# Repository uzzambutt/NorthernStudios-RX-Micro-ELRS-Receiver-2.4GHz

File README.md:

<p align="center">

</p>

<h1 align="center">Nano 2.4 GHz ExpressLRS Diversity PA/LNA Receiver</h1>

<p align="center">
  <strong>An ultra-compact (18×24 mm), open-hardware 2.4 GHz ExpressLRS receiver featuring true antenna diversity, a high-power FEM (+20 dBm telemetry), integrated Wi-Fi ceramic antenna, and paneled breakaway rails for low-cost JLCPCB PCBA.</strong>
</p>

<p align="center">
  <a href="#key-specifications--features">Key Specs</a> •
  <a href="#hero-visuals--3d-views">Visuals</a> •
  <a href="#schematic--system-architecture">Architecture</a> •
  <a href="#hardware-configuration--pinout">Pinout</a> •
  <a href="#pcb-fabrication--stackup-requirements">PCB Stackup</a> •
  <a href="#flashing--firmware-setup">Firmware Setup</a> •
  <a href="#bill-of-materials-bom--sourcing">BOM</a> •
  <a href="#license--regulatory-compliance">License</a>
</p>

---

## 1. Hero Visuals & 3D Views

<p align="center">
  
  <br>
  <em>Figure 1: Production 3D Top Render of the Nano 2.4 GHz ExpressLRS Diversity PA/LNA Receiver</em>
</p>

<details open>
<summary><b>🔍 Detailed 3D Perspective Comparison (Front & Back Views)</b></summary>
<br>

| Front Perspective (Core Silicon & RF Frontend) | Back Perspective (Passives, Testpads & Ground Plane) |
| :---: | :---: |
|  |  |
| **Top Side (L1):** ESP32-C3FH4, Semtech SX1280 Transceiver, Skyworks SE2431L PA/LNA FEM, 2450FM07D0034 Bandpass Filter, dual U.FL IPEX jacks, Johanson 2450AT ceramic chip antenna, status LED, crystals, and JST-GH connector. | **Bottom Side (L4):** Solid thermal relief stitching vias, dedicated USB test pads (USBD+/USBD-), BOOT strapping testpad, and low-impedance RF ground shield flood. |

</details>

---

## 2. Key Specifications & Features

The **NorthernStudios Nano 2.4 GHz ExpressLRS Diversity Receiver** is engineered for long-range, high-reliability UAV control links, telemetry backhaul, and high-interference drone racing / freestyle environments. Combining high-efficiency RISC-V computing with Semtech's SX1280 transceiver and Skyworks' SE2431L front-end module, it provides industrial-grade packet reception sensitivity, +20 dBm (100 mW) telemetry uplink, and seamless over-the-air firmware management.

### Executive Specification Matrix

| Category | Specification | Technical Implementation / Notes |
| :--- | :--- | :--- |
| **Microcontroller (MCU)** | **ESP32-C3FH4** | 32-bit RISC-V single-core @ 160 MHz, 400 KB SRAM, 4 MB embedded SiP SPI flash |
| **RF Transceiver** | **Semtech SX1280IMLTRT** | 2.4 GHz LoRa, FLRC, and high-speed FSK modulation engine (-132 dBm sensitivity) |
| **Front-End Module (FEM)** | **Skyworks SE2431L** | Fully integrated RF front-end: +22 dB PA, +12.5 dB LNA (2.0 dB NF), SP3T RF switch |
| **Telemetry Uplink Power** | **Up to 100 mW (+20 dBm)** | Dynamic/fixed telemetry power configurable via ExpressLRS WebUI and Lua scripts |
| **Primary Antenna Link** | **Dual U.FL / IPEX1 (ANT1 / ANT2)** | True spatial and polarization diversity switched dynamically per-packet |
| **Configuration Link** | **Johanson 2450AT18A100** | Dedicated onboard 2.45 GHz ceramic chip antenna for ESP32 Wi-Fi AP & WebUI |
| **RF Filtering** | **Johanson 2450FM07D0034** | Matched high-rejection 2.4 GHz ceramic bandpass filter / balun |
| **Active PCB Dimensions** | **16.0 × 22.0 mm** | Ultra-lightweight form factor suitable for sub-250g micros and long-range wings |
| **Board Interface Pads** | **2.54 mm Castellated Edges** | 4-pin direct solder pads (`5V`, `GND`, `TX`, `RX`) + sub-miniature test points |
| **Quick-Disconnect Plug** | **JST-GH 4-Pin Horizontal** | Standard 1.25 mm pitch connector for direct drone flight controller wire harness |
| **Panelized Manufacturing** | **70.0 × 70.0 mm Breakaway** | 0.6 mm perforated mouse-bite tabs, optical fiducials, and 3.2 mm tooling holes |
| **Power Input Range** | **4.5 V – 5.5 V DC** | Onboard high-efficiency, low-noise TSOT-23-5 LDO producing clean 3.3 V @ 500 mA |
| **Firmware Ecosystem** | **ExpressLRS v3.x / v4.x** | Custom unified target definition via runtime `hardware.json` or config profiles |

---

## 3. Schematic & Architecture

### System Schematic
The schematic is captured in KiCad 8/9 with complete hierarchical decoupling, controlled RF coplanar waveguides, and low-noise power distribution.

<p align="center">
  
  <br>
  <em>Figure 2: Complete Electrical Schematic — ESP32-C3FH4 Core, SX1280 2.4 GHz Transceiver, SE2431L Front-End Module, and Johanson RF Network</em>
</p>

### Architecture & Signal Flow

The receiver features two independent 2.4 GHz RF paths:
1. **LoRa / FLRC Flight Control Path:** Routes bidirectional RF signals between dual external U.FL dipole/immortal-T antennas, through the SE2431L SP3T switch, through the internal PA/LNA, through the matched 2450FM07D0034 bandpass filter, and into the Semtech SX1280 transceiver.
2. **Wi-Fi WebUI Configuration Path:** Connects the ESP32-C3's internal Wi-Fi/Bluetooth RF transceiver (`LNA_IN`) directly to an onboard Johanson 2450AT ceramic chip antenna through a precision 50Ω Grounded Coplanar Waveguide (GCPW), isolating telemetry link tuning from configuration management.

```mermaid
flowchart LR
    subgraph Antennas ["Antenna System"]
        A1["U.FL Antenna 1 (ANT1)"]
        A2["U.FL Antenna 2 (ANT2)"]
        AC["Johanson 2450AT Chip Antenna"]
    end

    subgraph FrontEnd ["RF Front-End (FEM)"]
        SW{"SE2431L SP3T Switch"}
        PA["Power Amp (+22 dB)"]
        LNA["Low Noise Amp (+12.5 dB)"]
    end

    subgraph Filtering ["RF Conditioning"]
        BPF["Johanson 2450FM07D0034 Filter"]
    end

    subgraph Silicon ["Core Transceiver & Processing"]
        SX["Semtech SX1280 Transceiver"]
        ESP["Espressif ESP32-C3FH4 (RISC-V)"]
    end

    subgraph Host ["Flight Controller Interface"]
        FC["Flight Controller (CRSF UART)"]
    end

    A1 <-->|"50Ω GCPW"| SW
    A2 <-->|"50Ω GCPW"| SW
    SW <-->|"TX Mode"| PA
    SW <-->|"RX Mode"| LNA
    PA <--> BPF
    LNA <--> BPF
    BPF <-->|"Balanced RF"| SX
    SX <-->|"High-Speed SPI + IRQ"| ESP
    AC <-->|"50Ω GCPW (Wi-Fi 802.11b/g/n)"| ESP
    ESP <-->|"CRSF Protocol (420k / 921k Baud)"| FC
```

#### ASCII Architecture Reference
```text
+---------------------------------------------------------------------------------------+
|                                    ANTENNA SYSTEM                                     |
|    [U.FL Port 1]                     [U.FL Port 2]            [Johanson 2450AT Chip]  |
|          |                                 |                             |            |
|          +----------------+----------------+                             |            |
|                           | (50Ω GCPW)                                   | (50Ω GCPW) |
|                           v                                              |            |
|       +---------------------------------------+                          |            |
|       |         Skyworks SE2431L FEM          |                          |            |
|       |  [ANT Switch] <-> [PA / +22dB]        |                          |            |
|       |               <-> [LNA / +12.5dB]     |                          |            |
|       +-------------------+-------------------+                          |            |
|                           ^                                              |            |
|                           | (Tx / Rx Enable & Ant Sel)                   |            |
|                           v                                              |            |
|       +---------------------------------------+                          |            |
|       |     Johanson 2450FM07D0034 Filter     |                          |            |
|       +-------------------+-------------------+                          |            |
|                           | (Matched Differential)                       |            |
|                           v                                              |            |
|       +---------------------------------------+                          |            |
|       |       Semtech SX1280 Transceiver      |                          |            |
|       |        2.4 GHz LoRa / FLRC / FSK      |                          |            |
|       +-------------------+-------------------+                          |            |
|                           |                                              |            |
|                           | SPI Bus (MOSI, MISO, SCK, NSS, BUSY, DIO1)   |            |
|                           v                                              v            |
|       +-----------------------------------------------------------------------+       |
|       |                     Espressif ESP32-C3FH4 Core                        |       |
|       |          32-bit RISC-V @ 160 MHz | 4MB Flash | 2.4 GHz Wi-Fi          |       |
|       +-----------------------------------+-----------------------------------+       |
|                                           |                                           |
|                           CRSF Telemetry  |  CRSF Serial RX                           |
|                           (GPIO20 - TX)   |  (GPIO21 - RX)                            |
|                                           v                                           |
|                         [Flight Controller UART Pad / JST-GH]                         |
+---------------------------------------------------------------------------------------+
```

---

## 4. Hardware Configuration & Pinout

The pin assignment is optimized for optimal trace routing on 4-layer PCBs, preserving signal integrity along high-speed SPI lines while isolating sensitive radio triggers from high-frequency clock harmonics.

### ExpressLRS Hardware Pin Mapping

| ESP32-C3 GPIO | Function / Net | ExpressLRS Definition | Description | Electrical Notes |
| :--- | :--- | :--- | :--- | :--- |
| **GPIO02** | `SX_RST` | `radio_rst` | SX1280 Hardware Reset | Active Low; internal pull-up |
| **GPIO03** | `SX_BUSY` | `radio_busy` | SX1280 Busy Status | Active High; polled before SPI transfers |
| **GPIO04** | `PWR_TXEN` | `power_txen` | SE2431L Transmit Enable | High = PA Transmit Mode; Low = LNA Receive Mode |
| **GPIO05** | `SX_DIO1` | `radio_dio1` | SX1280 Packet Interrupt | Active High; hardware interrupt for RX/TX events |
| **GPIO06** | `SCK` | `radio_sck` | Hardware SPI Clock | Up to 18 MHz SPI master bus clock |
| **GPIO07** | `MISO` | `radio_miso` | Hardware SPI Data In | Master-In Slave-Out from SX1280 |
| **GPIO08** | `ELRS_LED` | `led` | Receiver Status LED | Active Low; tied to 3.3V via current-limit resistor |
| **GPIO09** | `BOOT` | — | ESP32 Strapping / Boot | Pulled High internally; pull to GND for DFU UART flash |
| **GPIO10** | `ANT_SEL` | `ant_ctrl` | SE2431L Antenna Switch | High = Antenna 2 (ANT2); Low = Antenna 1 (ANT1) |
| **GPIO12** | `MOSI` | `radio_mosi` | Hardware SPI Data Out | Master-Out Slave-In to SX1280 |
| **GPIO13** | `SX_NSS` | `radio_nss` | SX1280 Chip Select | Active Low SPI slave select |
| **GPIO20** | `U0RXD` | `serial_tx` | ExpressLRS CRSF TX | Transmits CRSF packet frames to Flight Controller RX |
| **GPIO21** | `U0TXD` | `serial_rx` | ExpressLRS CRSF RX | Receives serial channel/telemetry from Flight Controller TX |

### External Connector & Pad Pinout

```text
       +---------------------------------------------+
       | [ANT1]                               [ANT2] |
       |                                             |
       |  (1) 5V   [ 4.5V - 5.5V DC Input ]          |
       |  (2) GND  [ Power & Signal Ground ]         |  Active PCB Area:
       |  (3) TX   [ CRSF Telemetry to FC RX ]       |  16.0 x 22.0 mm
       |  (4) RX   [ CRSF Control from FC TX ]       |
       |                                             |
       | [JST-GH] (1:GND, 2:5V, 3:TX, 4:RX)          |
       | [TP_BOOT] [TP_USBD-] [TP_USBD+]             |
       +---------------------------------------------+
```

* **Castellated Solder Pads (Edge J3–J6):** Standard 2.54 mm (0.1") pitch for direct wire soldering or header pins.
* **Micro-Connector (J7):** JST-GH 4-pin horizontal locking receptacle (1.25 mm pitch) matching modern flight controllers (Matek, SpeedyBee, Holybro, BetaFPV).
* **Test Points:** Dedicated pads for `BOOT` (J10/J11), `USBD-` (TP1), and `USBD+` (TP2) for debugging or manual recovery.

---

## 5. PCB Fabrication & Stackup Requirements

The board utilizes a 4-layer controlled-impedance stackup specifically tailored for the **JLCPCB JLC04161H-3313** or **JLC04161H-7628** process.

<p align="center">
  
  <br>
  <em>Figure 3: 4-Layer Controlled-Impedance Stackup (0.1 mm Prepreg / 1.6 mm Total Board Thickness)</em>
</p>

### Layer Stack Architecture

| Layer | Type | Copper Thickness | Material | Description & RF Design Rules |
| :--- | :--- | :--- | :--- | :--- |
| **L1 (Top)** | Signal / RF | 1 oz (0.035 mm) | Copper | **High-frequency 50Ω GCPW traces**, critical components, antenna feed lines |
| *Dielectric 1* | Core/Prepreg | 0.100 mm | FR4 (εr ≈ 4.5) | Prepreg layer providing tight capacitive coupling to Layer 2 GND |
| **L2 (Inner 1)** | Plane | 1 oz (0.035 mm) | Copper | **Solid unbroken Ground reference plane**. Zero cutouts under RF traces |
| *Dielectric 2* | Core | 1.240 mm | FR4 (εr ≈ 4.5) | Rigid structural core isolating RF ground from digital power routing |
| **L3 (Inner 2)** | Power / Signal | 1 oz (0.035 mm) | Copper | Clean 3.3V power rails, LDO decoupling, non-critical control signals |
| *Dielectric 3* | Core/Prepreg | 0.100 mm | FR4 (εr ≈ 4.5) | Dielectric insulation layer |
| **L4 (Bottom)** | Signal / Ground | 1 oz (0.035 mm) | Copper | Secondary ground flood, thermal vias, testpoints, and passive return paths |

### RF Coplanar Waveguide Specifications
* **50Ω GCPW Trace Width ($W$):** `0.18 mm` (7.1 mil)
* **Trace-to-Ground Clearance ($S$):** `0.15 mm` (5.9 mil)
* **Dielectric Height ($H$):** `0.10 mm` (Prepreg to Layer 2 GND)
* **Ground Via Pitch:** Continuous via stitching with $\le 1.0\text{ mm}$ center-to-center spacing along all RF microstrips to suppress substrate resonance.

### Panel & Breakaway Frame Handling
The receiver is fabricated in a standardized **70 × 70 mm manufacturing panel frame** containing:
* **Tooling Holes:** 4× 3.2 mm non-plated holes located at panel corners for automated high-speed SMT feeders.
* **Optical Fiducials:** 3× 1.0 mm round copper fiducials with 2.0 mm soldermask openings for machine vision alignment.
* **Breakaway Tabs:** 0.6 mm perforated mouse bites with center drill holes on each breakaway edge.

> [!TIP]
> **Post-Reflow Breakaway Removal Instructions:**
> 1. Score the mouse bite tabs lightly using an engineer's carbide scribe or hobby hobby knife on both sides.
> 2. Support the active receiver body flat against a bench surface and bend the outer rails downward with gentle, even pressure.
> 3. Clip remaining nibs flush using precision flush cutters (e.g. Plato 170).
> 4. Lightly dress the castellated edges with 400-grit abrasive paper to ensure no copper burrs short against the edge ground plane.

---

## 6. Flashing & Firmware Setup

### Method 1: Initial UART Bootloader Flash (First-Time Commissioning)

1. Connect the receiver to a 3.3V USB-to-UART adapter (CP2102, FT232RL, or CH340):
   * `5V` $\rightarrow$ `5V` (or external clean 5V supply)
   * `GND` $\rightarrow$ `GND`
   * `TX` $\rightarrow$ Adapter `RX`
   * `RX` $\rightarrow$ Adapter `TX`
2. **Engage Bootloader:** Bridge the **`BOOT`** test pad (GPIO09) to **`GND`** using tweezers or a jumper wire, then connect USB power to the adapter. Release the bridge after power is applied.
3. Open **ExpressLRS Configurator** (v1.6.0+):
   * **Target:** `Generic target using ESP32-C3` (or choose unified target)
   * **Device:** `Generic ESP32-C3 2.4GHz RX`
   * **Flashing Method:** `UART`
   * Set your **Binding Phrase**, regulatory domain (`FCC` / `LBT`), and Wi-Fi credentials.
4. Click **Build & Flash**. Once flashing is complete, power-cycle the board.

---

### Method 2: Wi-Fi Over-The-Air (OTA) Updating (Recommended)

1. Power the receiver via flight controller or a 5V bench supply.
2. Leave your radio transmitter powered off. After **60 seconds**, the receiver will automatically switch into Wi-Fi Access Point mode.
3. The onboard status LED (`D1`) will begin rapidly blinking (5 Hz).
4. Connect your PC or smartphone to the Wi-Fi network:
   * **SSID:** `ExpressLRS RX`
   * **Password:** `expresslrs`
5. Navigate your browser to `http://10.0.0.1` (or `http://elrs_rx.local`).
6. Upload the updated `.bin` firmware file or modify runtime configuration values directly via the WebUI.

---

### Custom Target Definition (`hardware.json`)

To load the hardware pinout dynamically on unified ExpressLRS firmware builds, navigate to the **Hardware** tab in the WebUI and paste the following target definition:

```json
{
  "target": "NS_ELRS_RX_MICRO_2400",
  "name": "NorthernStudios Nano 2.4GHz Diversity RX",
  "brand": "NorthernStudios",
  "radio": "sx1280",
  "mcu": "esp32c3",
  "serial_rx": 21,
  "serial_tx": 20,
  "radio_busy": 3,
  "radio_dio1": 5,
  "radio_miso": 7,
  "radio_mosi": 12,
  "radio_nss": 13,
  "radio_rst": 2,
  "radio_sck": 6,
  "power_txen": 4,
  "ant_ctrl": 10,
  "led": 8,
  "led_inverted": true,
  "power_min": 0,
  "power_high": 3,
  "power_max": 3,
  "power_default": 0,
  "power_control": 1,
  "power_values": [-18, -13, -9, -5, -2, 0, 3, 6, 10, 13]
}
```

---

## 7. Bill of Materials (BOM) & Sourcing

Every active IC, passive, and connector has been selected for high performance, standard commercial availability, and turnkey automated assembly via JLCPCB SMT / LCSC.

### Core Active Silicon & RF Front-End

| Designator | Value / Part Number | Manufacturer | Description & Package | LCSC Part # | Sourcing Link |
| :--- | :--- | :--- | :--- | :--- | :--- |
| **U1** | **ESP32-C3FH4** | Espressif Systems | 32-bit RISC-V SoC, 4MB Flash, QFN-32 (5×5 mm) | Standard | [Datasheet](https://www.espressif.com/sites/default/files/documentation/esp32-c3_datasheet_en.pdf) |
| **U2** | **SX1280IMLTRT** | Semtech Corp. | 2.4 GHz LoRa/FLRC Transceiver, QFN-24 (4×4 mm) | Standard | [Datasheet](https://www.semtech.com/products/wireless-rf/24-ghz/sx1280) |
| **U6** | **SE2431L-R** | Skyworks Solutions | High-Power FEM (PA + LNA + SP3T Switch), QFN-24 (3×4 mm) | **C2649471** | [Datasheet](https://www.skyworksinc.com/-/media/SkyWorks/Documents/Products/1801-1900/SE2431L_202410L.pdf) |
| **U3** | **SGM2036-3.3** / TSOT23 | SG Micro / Anyleaf | High PSRR, 500mA LDO Regulator, TSOT-23-5 | **C587158** | [LCSC](https://www.lcsc.com/product-detail/Linear-Voltage-Regulators-LDO_SGMICRO-SGM2036-3-3YN5G-TR_C587158.html) |
| **FL1** | **2450FM07D0034** | Johanson Technology | Matched 2.45 GHz Bandpass Filter/Balun, SMD-1109 | Standard | [Johanson](https://www.johansontechnology.com/datasheets/2450FM07D0034/2450FM07D0034.pdf) |
| **AE1** | **2450AT18A100** | Johanson Technology | 2.45 GHz Ceramic Chip Antenna, SMD-3216 (1206) | Standard | [Johanson](https://www.johansontechnology.com/datasheets/antennas/2450AT18A100.pdf) |

### Crystals, Connectors & Passives

| Designator | Quantity | Value / Specification | Footprint / Package | LCSC Part # | Notes |
| :--- | :---: | :--- | :--- | :--- | :--- |
| **Y1** | 1 | **52 MHz, 8 pF, ±10 ppm** | Crystal SMD 2016-4P (2.0×1.6 mm) | Standard | SX1280 Reference Clock |
| **Y2** | 1 | **40 MHz, 8 pF, ±10 ppm** | Crystal SMD 2520-4P (2.5×2.0 mm) | Standard | ESP32-C3 Reference Clock |
| **J1, J2** | 2 | **U.FL-R-SMT-1** (IPEX1) | Micro-Coaxial Surface Mount Jack | Standard | ANT1 / ANT2 RF Connectors |
| **J7** | 1 | **SM04B-GHS-TB (LF)(SN)** | 4-Pin 1.25 mm Horizontal JST-GH | **C189895** | Flight Controller Harness |
| **D1** | 1 | **LED Emerald Green / Blue** | SMD 0603 (1608 Metric) | Standard | Status Indicator (Active Low) |
| **L1, L2** | 2 | **3.0 nH High-Q Inductor** | SMD 0402 (1005 Metric) | Standard | RF Matching Network |
| **L3** | 1 | **15 µH Power Inductor** | SMD 0805 (2012 Metric) | Standard | SX1280 DC-DC Buck Filter |
| **C1** | 1 | **1 µF 10V X5R** | SMD 0402 (1005 Metric) | **C52923** | Decoupling |
| **C2** | 1 | **2.2 µF 10V X5R** | SMD 0402 (1005 Metric) | **C12530** | LDO Output Bypass |
| **C3, C5** | 2 | **10 pF 50V C0G/NP0** | SMD 0402 (1005 Metric) | Standard | RF Decoupling |
| **C6, C7, C8, C9**| 4 | **1.2 pF 50V C0G/NP0** | SMD 0402 (1005 Metric) | Standard | RF Matching / Tuning |
| **C4, C11, C12** | 3 | **100 nF 16V X7R** | SMD 0402 (1005 Metric) | Standard | Digital Decoupling |
| **C10, C13** | 2 | **10 nF 50V X7R** | SMD 0402 (1005 Metric) | Standard | RF Power Rail Decoupling |
| **C14** | 1 | **470 nF 10V X5R** | SMD 0402 (1005 Metric) | Standard | Transceiver VDD |
| **C15** | 1 | **10 µF 10V X5R** | SMD 0402 (1005 Metric) | Standard | LDO Bulk Decoupling |
| **C16, C19, C22**| 3 | **1 µF 10V X5R** | SMD 0402 (1005 Metric) | Standard | Power Rail Smoothing |
| **C17, C18** | 2 | **0.1 µF 16V X7R** | SMD 0402 (1005 Metric) | Standard | Core Filtering |
| **C20, C21** | 2 | **12 pF 50V C0G/NP0** | SMD 0402 (1005 Metric) | Standard | Crystal Load Capacitors |
| **R1** | 1 | **100 kΩ 1%** | SMD 0402 (1005 Metric) | Standard | Pull-down / Pull-up |
| **R2** | 1 | **2.2 kΩ 1%** | SMD 0402 (1005 Metric) | Standard | Pull-up |
| **R3** | 1 | **1.2 kΩ 1%** | SMD 0402 (1005 Metric) | Standard | LED Bias Limiter |
| **R4, R6, R7, R9**| 4 | **10 kΩ 1%** | SMD 0402 (1005 Metric) | **C25744** | Reset & Mode Strapping |
| **R5** | 1 | **0 Ω Jumper** | SMD 0201 (0603 Metric) | Standard | RF Option Bridge |
| **R8** | 1 | **1 kΩ 1%** | SMD 0201 (0603 Metric) | Standard | Pull-up |

---

## 8. License & Regulatory Compliance

### Open Hardware License
This project is licensed under the **[CERN Open Hardware Licence Version 2 – Strongly Reciprocal (CERN-OHL-S-v2)](https://ohwr.org/cern_ohl_s_v2.txt)**.
* **Hardware Design Files:** You may modify, manufacture, distribute, and sell this hardware, provided that any derivative designs or modifications are released under the exact same CERN-OHL-S-v2 terms.
* **Documentation & Media:** All accompanying schematics, 3D renders, diagrams, and written documentation are released under [CC BY-SA 4.0](https://creativecommons.org/licenses/by-sa/4.0/).

### Regulatory Notice & Amateur Radio Compliance

> [!WARNING]
> **Radio Frequency Operating Compliance:**
> This receiver is an open-source development device operating within the 2.400 GHz – 2.4835 GHz ISM band. Telemetry uplink operations can emit up to **+20 dBm (100 mW) EIRP**.
> * **Amateur Radio Licensing:** Depending on your jurisdiction, transmitting at elevated telemetry power levels (+20 dBm) may require a valid Amateur Radio (Ham) license.
> * **European Union (CE / RED):** Users operating within CE-compliant jurisdictions must configure ExpressLRS to use **LBT (Listen-Before-Talk)** mode with EIRP restricted to $\le 10\text{ dBm}$ (10 mW) or $\le 20\text{ dBm}$ with active LBT duty-cycling.
> * **United States (FCC Part 15 / Part 97):** Operation must comply with FCC rules governing digital transmission systems within the 2.4 GHz band.
> The authors and contributors assume no liability for non-compliant RF transmission or unauthorized frequency usage.

---

## 9. Contributing & Acknowledgments

Contributions, issue reports, and pull requests are welcomed!
* For hardware bug reports, impedance recalculations, or BOM alternatives, please open an issue or pull request against this repository.
* For firmware features and telemetry protocol questions, please consult the upstream [ExpressLRS Project](https://github.com/ExpressLRS/ExpressLRS).

### Acknowledgments
* **[ExpressLRS Team](https://www.expresslrs.org/):** For developing the world's most performant open-source RC radio link.
* **[Semtech Corporation](https://www.semtech.com/):** For the exceptional SX1280 2.4 GHz LoRa/FLRC silicon.
* **[Espressif Systems](https://www.espressif.com/):** For the ESP32-C3 RISC-V SoC architecture.
* **[Skyworks Solutions](https://www.skyworksinc.com/):** For the SE2431L high-efficiency RF front-end module.
* **[KiCad Development Community](https://www.kicad.org/):** For providing the world-class open-source EDA suite.

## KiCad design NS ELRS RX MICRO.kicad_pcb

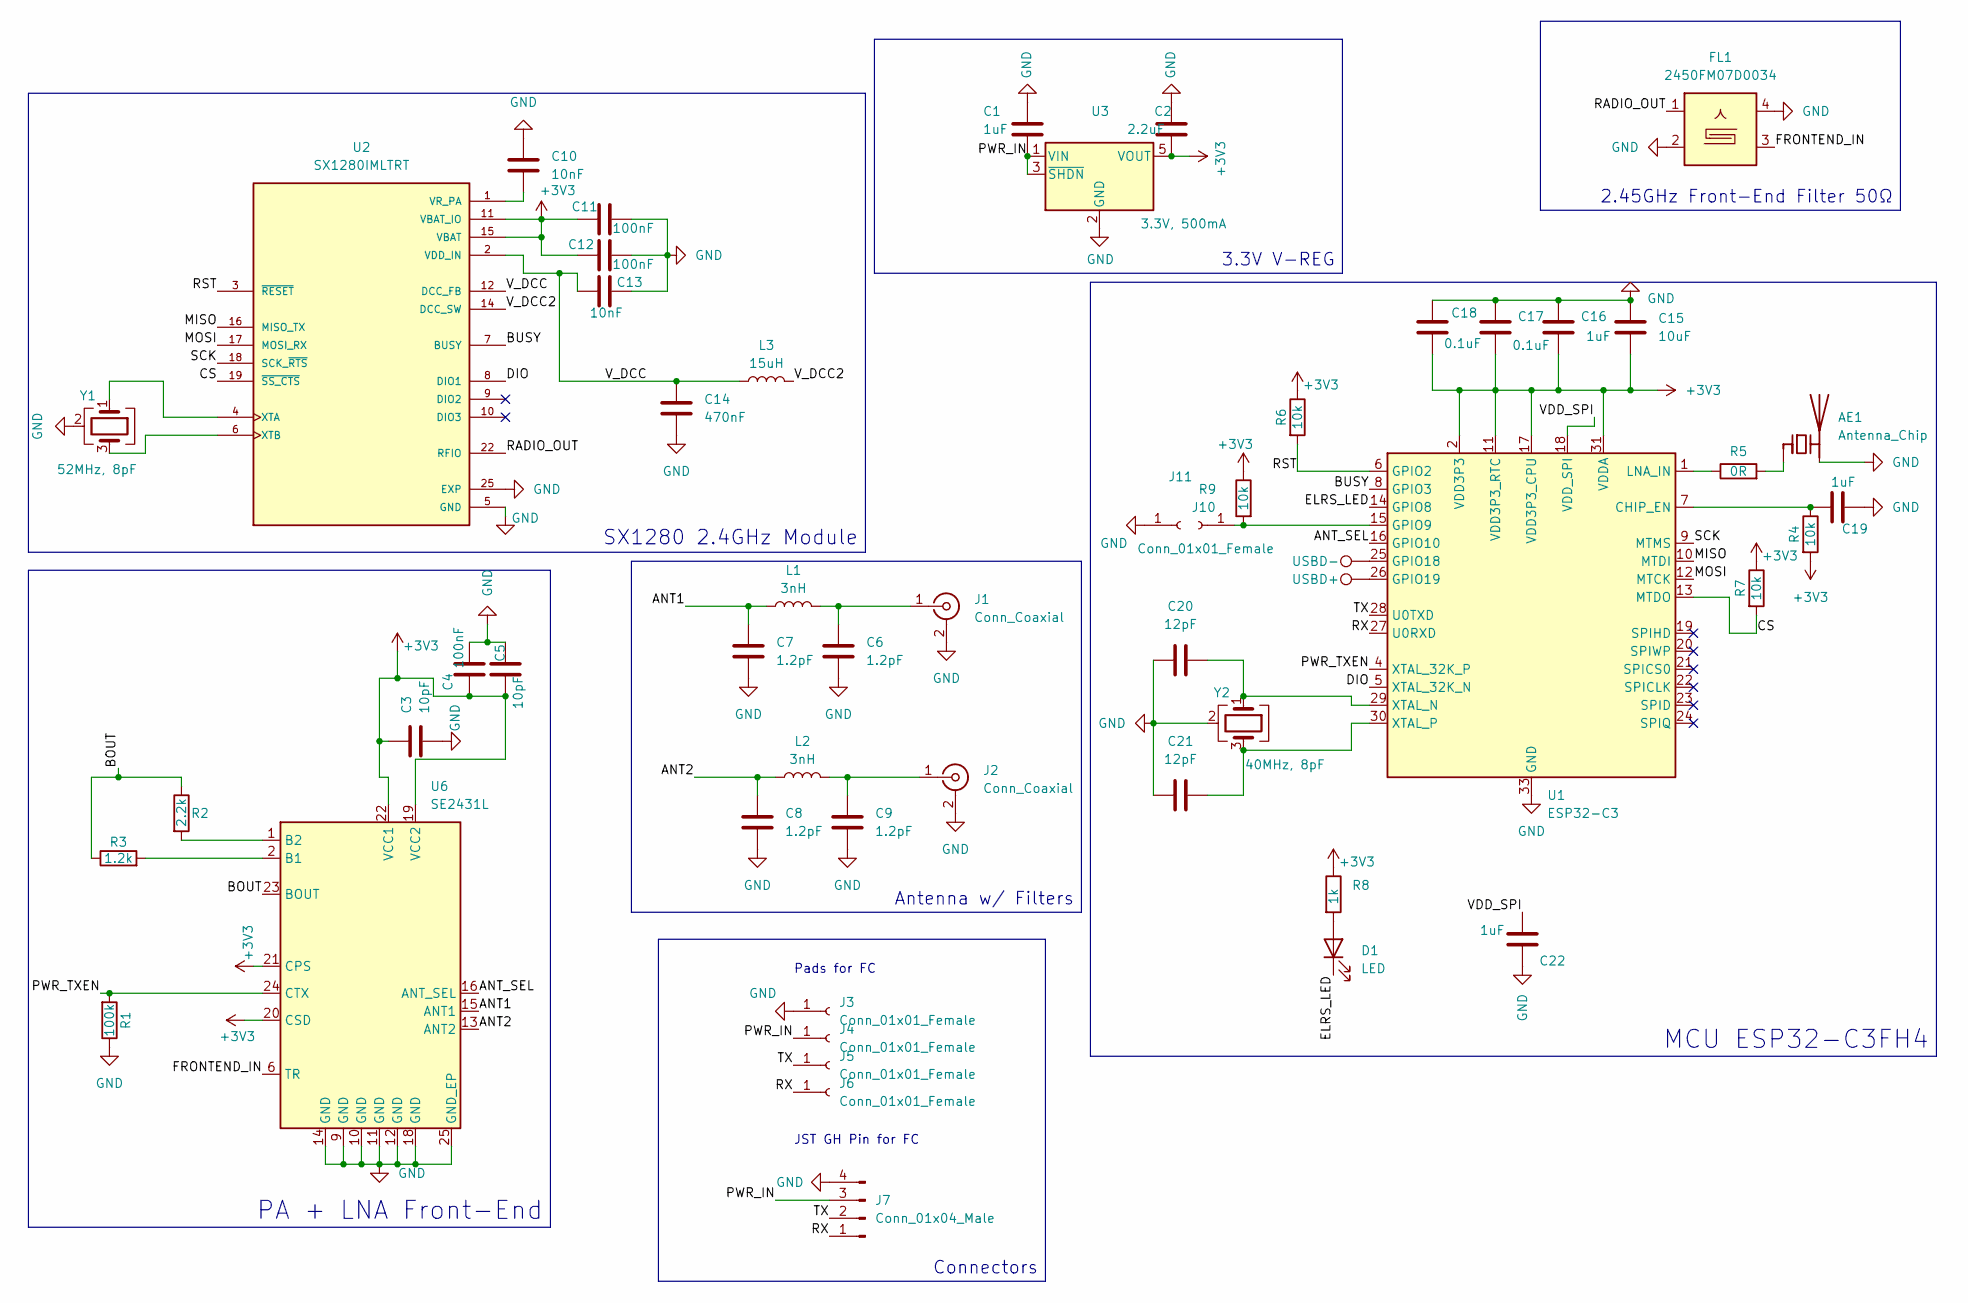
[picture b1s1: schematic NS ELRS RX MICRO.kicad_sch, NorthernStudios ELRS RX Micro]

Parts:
AE1: Antenna_Chip; Johanson_2450AT18x100
C1: 1uF; C_0402_1005Metric; LCSC C52923
C2: 2.2uF; C_0402_1005Metric; LCSC C12530
C3, C5: 10pF; C_0402_1005Metric
C4, C11, C12: 100nF; C_0402_1005Metric
C6, C7, C8, C9: 1.2pF; C_0402_1005Metric
C10, C13: 10nF; C_0402_1005Metric
C14: 470nF; C_0402_1005Metric
C15: 10uF; C_0402_1005Metric
C16, C19, C22: 1uF; C_0402_1005Metric
C17, C18: 0.1uF; C_0402_1005Metric
C20, C21: 12pF; C_0402_1005Metric
D1: LED; LED_0603_1608Metric
FL1: 2450FM07D0034
J1, J2: Conn_Coaxial; U.FL_Hirose_U.FL-R-SMT-1_Vertical
J3, J4, J5, J6: Conn_01x01_Female; TestPoint_Pad_2.5x2.5mm
J7: Conn_01x04_Male; JST_GH_SM04B-GHS-TB_1x04-1MP_P1.25mm_Horizontal; LCSC C189895
J10, J11: Conn_01x01_Female; TestPoint_Pad_1.0x1.0mm
L1, L2: 3nH; L_0402_1005Metric
L3: 15uH; L_0805_2012Metric
R1: 100k; R_0402_1005Metric
R2: 2.2k; R_0402_1005Metric
R3: 1.2k; R_0402_1005Metric
R4, R6, R7: 10k; R_0402_1005Metric
R5: 0R; R_0201_0603Metric
R8: 1k; R_0201_0603Metric
R9: 10k; R_0402_1005Metric; LCSC C25744
TP1: USBD-; TestPoint_Pad_1.0x1.0mm
TP2: USBD+; TestPoint_Pad_1.0x1.0mm
U1: ESP32-C3; QFN-32-1EP_5x5mm_P0.5mm_EP3.7x3.7mm
U2: SX1280IMLTRT; XCVR_SX1280IMLTRT; PARTREV 3.3
U3: 3.3V, 500mA; TSOT-23-5; Part TPRT9013-33GB; LCSC C587158
U6: SE2431L; QFN-24-1EP_3x4mm_P0.4mm_EP1.65x2.65mm; Digikey 863-1347-2-ND
Y1: 52MHz, 8pF; Crystal_SMD_2016-4Pin_2.0x1.6mm
Y2: 40MHz, 8pF; Crystal_SMD_2520-4Pin_2.5x2.0mm

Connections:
+3V3: C2.2, C3.1, C4.1, C5.1, C11.2, C12.2, C15.2, C16.2, C17.2, C18.2, R4.2, R6.1, R7.1, R8.1, R9.1, U1.2 (VDD3P3), U1.3 (VDD3P3), U1.11 (VDD3P3_RTC), U1.17 (VDD3P3_CPU), U1.31 (VDDA), U1.32 (VDDA), U2.11 (VBAT_IO), U2.15 (VBAT), U3.5 (VOUT), U6.19 (VCC2), U6.20 (CSD), U6.21 (CPS), U6.22 (VCC1)
/ANT1: C7.1, L1.1, U6.15 (ANT1)
/ANT2: C8.1, L2.1, U6.13 (ANT2)
/ANT_SEL: U1.16 (GPIO10), U6.16 (ANT_SEL)
/BOUT: R2.1, R3.1, U6.23 (BOUT)
/BUSY: U1.8 (GPIO3), U2.7 (BUSY)
/CS: R7.2, U1.13 (MTDO), U2.19 (~SS_CTS)
/DIO: U1.5 (XTAL_32K_N), U2.8 (DIO1)
/ELRS_LED: D1.1 (K), U1.14 (GPIO8)
/FRONTEND_IN: FL1.3, U6.6 (TR)
/MISO: U1.10 (MTDI), U2.16 (MISO_TX)
/MOSI: U1.12 (MTCK), U2.17 (MOSI_RX)
/PWR_IN: C1.2, J4.1, J7.3, U3.1 (VIN), U3.3 (~SHDN); also elsewhere on the board
/PWR_TXEN: R1.2, U1.4 (XTAL_32K_P), U6.24 (CTX)
/RADIO_OUT: FL1.1, U2.22 (RFIO)
/RST: R6.2, U1.6 (GPIO2), U2.3 (~RESET)
/RX: J6.1, J7.1, U1.27 (U0RXD); also elsewhere on the board
/SCK: U1.9 (MTMS), U2.18 (SCK_~RTS)
/TX: J5.1, J7.2, U1.28 (U0TXD); also elsewhere on the board
/VDD_SPI: C22.1, U1.18 (VDD_SPI)
/V_DCC: C13.2, C14.1, L3.1, U2.2 (VDD_IN), U2.12 (DCC_FB)
/V_DCC2: L3.2, U2.14 (DCC_SW)
GND: AE1.2 (PCB_Trace), C1.1, C2.1, C3.2, C4.2, C5.2, C6.2, C7.2, C8.2, C9.2, C10.2, C11.1, C12.1, C13.1, C14.2, C15.1, C16.1, C17.1, C18.1, C19.1, C20.1, C21.1, C22.2, FL1.2, FL1.4, FL1.5, J1.2 (Ext), J2.2 (Ext), J3.1 (Pin_1_1), J7.4, J11.1 (Pin_1_1), R1.1, U1.33 (GND), U2.5 (GND), U2.13 (GND), U2.20 (GND), U2.21 (GND), U2.23 (GND), U2.24 (GND), U2.25 (EXP), U3.2 (GND), U6.9 (GND), U6.10 (GND), U6.11 (GND), U6.12 (GND), U6.14 (GND), U6.18 (GND), U6.25 (GND_EP), Y1.2 (G), Y1.4 (G), Y2.2 (G), Y2.4 (G)
unnamed: AE1.1 (FEED), R5.2
unnamed: D1.2 (A), R8.2
unnamed: C6.1, J1.1 (In), L1.2
unnamed: C9.1, J2.1 (In), L2.2
unnamed: J10.1 (Pin_1_1), R9.2, U1.15 (GPIO9)
unnamed: C19.2, R4.1, U1.7 (CHIP_EN)
unnamed 29: TP1.1, U1.25 (GPIO18); also elsewhere on the board
unnamed 30: TP2.1, U1.26 (GPIO19); also elsewhere on the board
unnamed: R5.1, U1.1 (LNA_IN)
unnamed: C20.2, U1.29 (XTAL_N), Y2.1
unnamed: C21.2, U1.30 (XTAL_P), Y2.3
unnamed: C10.1, U2.1 (VR_PA)
unnamed: U2.4 (XTA), Y1.1
unnamed: U2.6 (XTB), Y1.3
unnamed: R3.2, U6.2 (B1)
unnamed: R2.2, U6.1 (B2)

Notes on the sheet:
JST GH Pin for FC
Pads for FC
MCU ESP32-C3FH4
SX1280 2.4GHz Module
PA + LNA Front-End
2.45GHz Front-End Filter 50Ω
3.3V V-REG
Antenna w/ Filters
Connectors

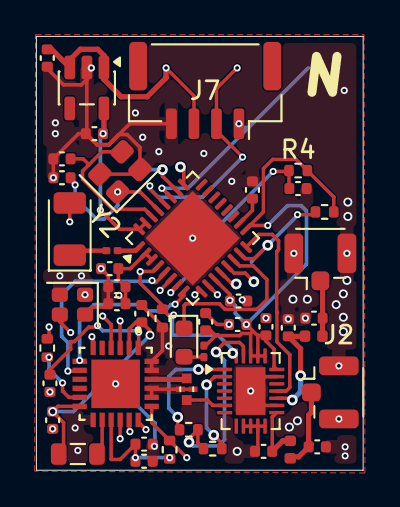
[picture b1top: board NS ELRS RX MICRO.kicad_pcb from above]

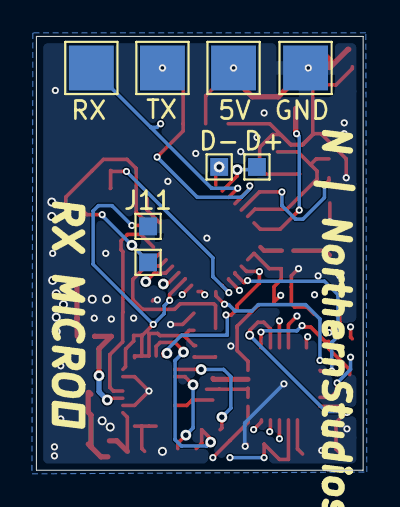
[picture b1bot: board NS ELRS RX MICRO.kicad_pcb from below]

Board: 4 copper layers, 18.2 x 24.1 mm, 54 parts (8 on the bottom side), 39 nets.

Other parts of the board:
5V: Conn_01x01_Female; TestPoint_Pad_2.5x2.5mm
D+: USBD+; TestPoint_Pad_1.0x1.0mm
D-: USBD-; TestPoint_Pad_1.0x1.0mm
RX: Conn_01x01_Female; TestPoint_Pad_2.5x2.5mm
TX: Conn_01x01_Female; TestPoint_Pad_2.5x2.5mm

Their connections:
/PWR_IN: 5V.1 (Pin_1_1); also elsewhere on the board
/RX: RX.1 (Pin_1_1); also elsewhere on the board
/TX: TX.1 (Pin_1_1); also elsewhere on the board
unnamed 29: D-.1 (1_1); also elsewhere on the board
unnamed 30: D+.1 (1_1); also elsewhere on the board

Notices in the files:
README.md:
License: CERN-OHL-S-v2
